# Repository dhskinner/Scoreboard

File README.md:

# Scoreboard
Sports Club Scoreboard

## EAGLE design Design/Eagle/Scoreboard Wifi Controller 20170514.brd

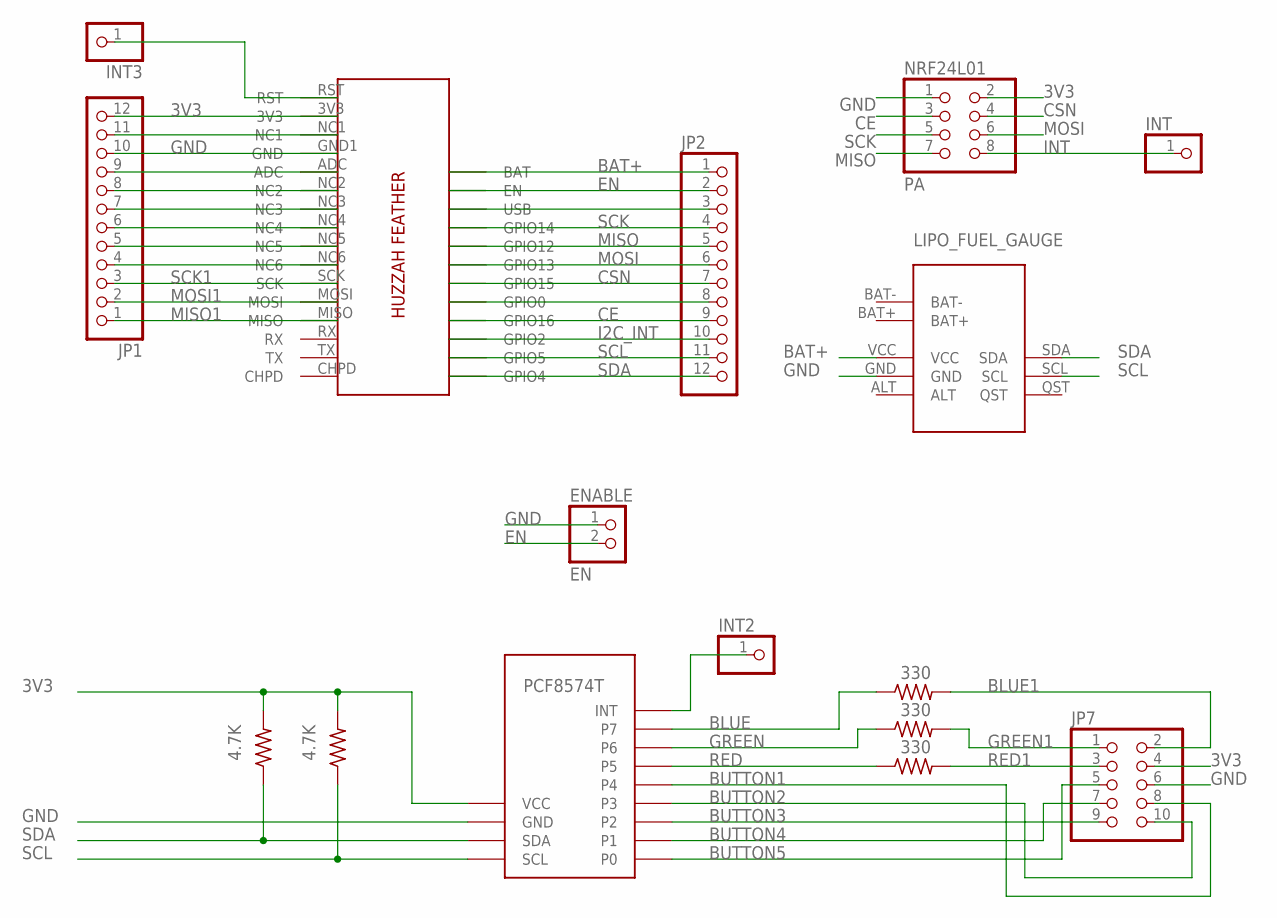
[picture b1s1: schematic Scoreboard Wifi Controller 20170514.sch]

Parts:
ENABLE: EN; 1X02/90
INT, INT2, INT3: PINHD-1X1CB; 1X01-CLEANBIG
JP1, JP2: PINHD-1X12-CB; 1X12-CB
JP7: PINHD-2X5/90; 2X05/90
LIPO_FUEL_GAUGE: LIPO_FUEL_GAUGE
NRF24L01: PA; 2X04/90
R2, R3, R4: 330; 0207/10
R5, R6: 4.7K; 0207/10
U$1: ADAFRUIT-FEATHER-ESP8266-HUZZAHALT; ADAFRUIT-FEATHER-ESP8266-HUZZAH-ALT
U$3: PCF8574T_IO_EXPANDER

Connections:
3V3: JP1.12, JP7.4, NRF24L01.2, R5.2, R6.2, U$1.3V3, U$3.VCC
BAT+: JP2.1, LIPO_FUEL_GAUGE.VCC, U$1.BAT
BLUE: R2.1, U$3.P$7 (P7)
BLUE1: JP7.2, R2.2
BUTTON1: JP7.8, U$3.P$4 (P4)
BUTTON2: JP7.10, U$3.P$3 (P3)
BUTTON3: JP7.9, U$3.P$2 (P2)
BUTTON4: JP7.7, U$3.P$1 (P1)
BUTTON5: JP7.5, U$3.P$0 (P0)
CE: JP2.9, NRF24L01.3, U$1.GPIO16
CSN: JP2.7, NRF24L01.4, U$1.GPIO15
EN: ENABLE.2, JP2.2, U$1.EN
GND: ENABLE.1, JP1.10, JP7.6, LIPO_FUEL_GAUGE.GND, NRF24L01.1, U$1.GND1 (GND), U$3.GND
GREEN: R3.1, U$3.P$6 (P6)
GREEN1: JP7.1, R3.2
I2C_INT: INT2.1, JP2.10, U$1.GPIO2, U$3.INT
INT: INT.1, NRF24L01.8
MISO: JP2.5, NRF24L01.7, U$1.GPIO12
MISO1: JP1.1, U$1.MISO
MOSI: JP2.6, NRF24L01.6, U$1.GPIO13
MOSI1: JP1.2, U$1.MOSI
unnamed: JP1.9, U$1.ADC
unnamed: JP2.8, U$1.GPIO0
unnamed: JP2.3, U$1.USB
unnamed: JP1.8, U$1.NC2
unnamed: JP1.7, U$1.NC3
unnamed: JP1.6, U$1.NC4
unnamed: JP1.5, U$1.NC5
unnamed: JP1.4, U$1.NC6
unnamed: JP1.11, U$1.NC1
RED: R4.1, U$3.P$5 (P5)
RED1: JP7.3, R4.2
RST: INT3.1, U$1.RST
SCK: JP2.4, NRF24L01.5, U$1.GPIO14
SCK1: JP1.3, U$1.SCK
SCL: JP2.11, LIPO_FUEL_GAUGE.SCL, R5.1, U$1.GPIO5, U$3.SCL
SDA: JP2.12, LIPO_FUEL_GAUGE.SDA, R6.1, U$1.GPIO4, U$3.SDA

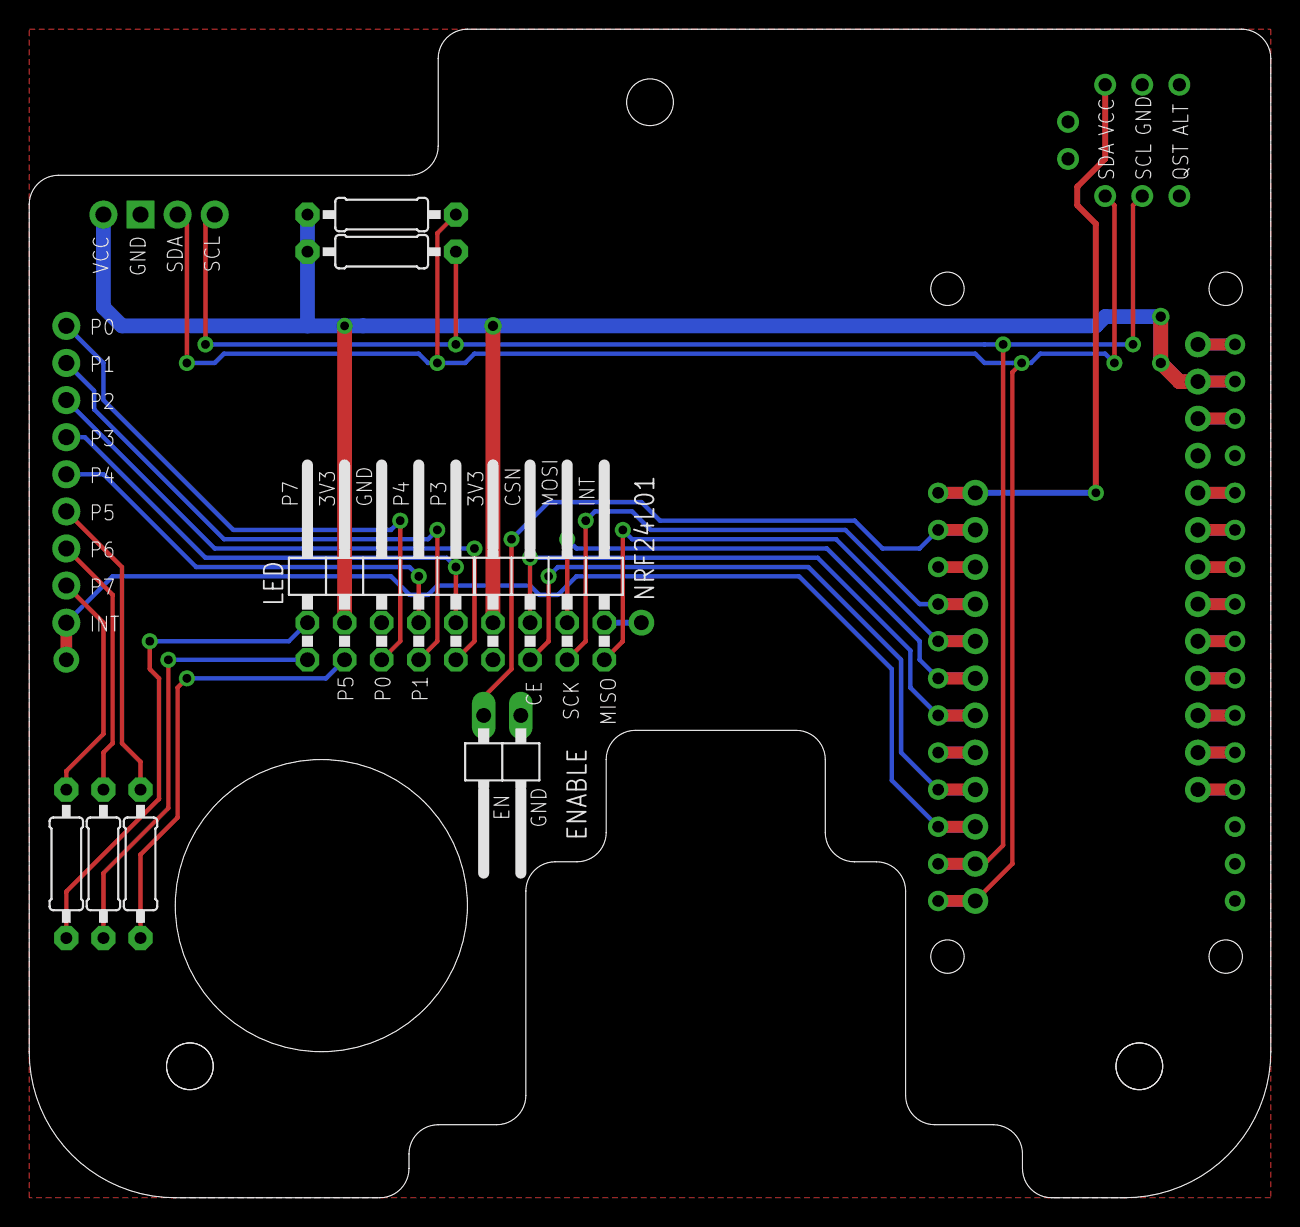
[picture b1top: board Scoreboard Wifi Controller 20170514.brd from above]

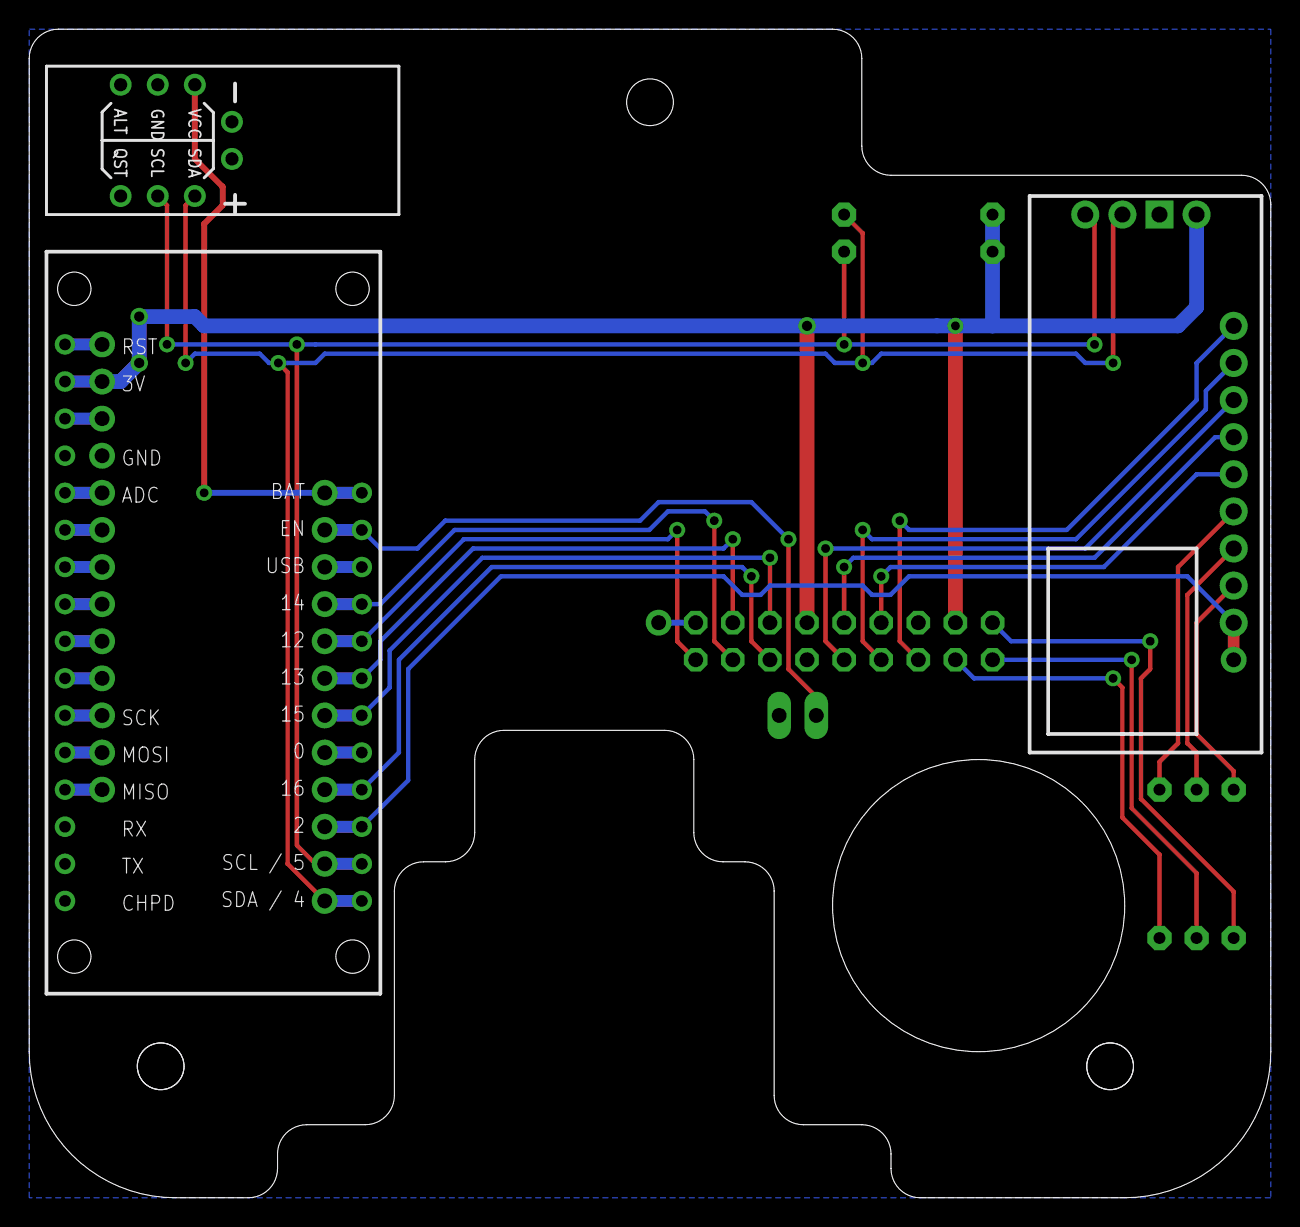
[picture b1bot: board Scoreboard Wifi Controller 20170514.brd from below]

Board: 2 copper layers, 85.0 x 80.0 mm, 16 parts (3 on the bottom side), 37 nets.

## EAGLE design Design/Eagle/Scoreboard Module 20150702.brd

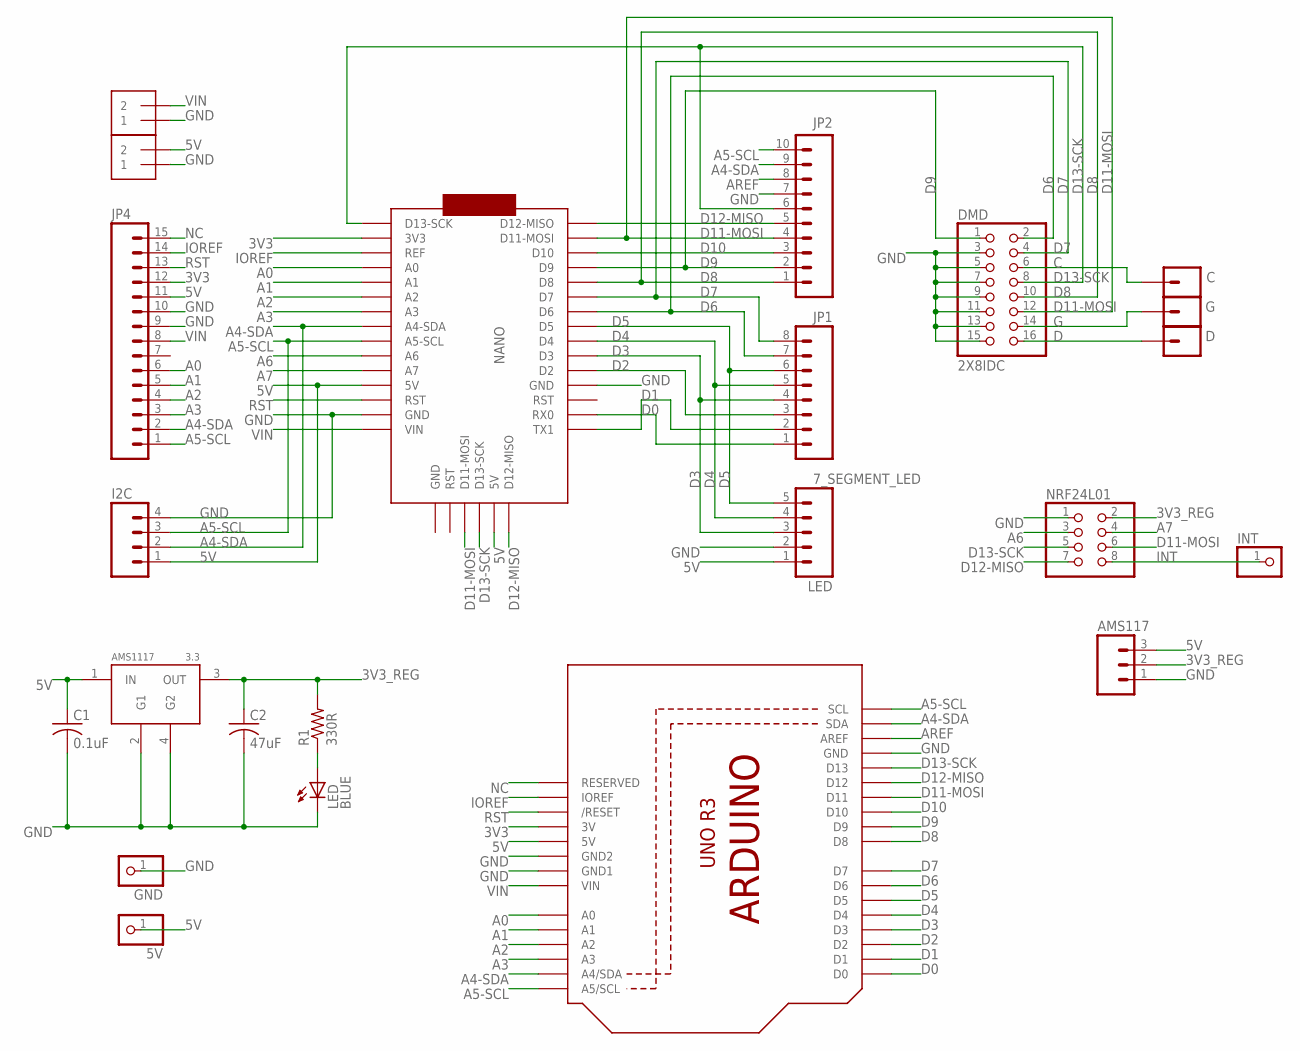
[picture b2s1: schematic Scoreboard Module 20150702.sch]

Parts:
5V: PINHD-1X1; 1X01
7_SEGMENT_LED: LED; 1X05
AMS117: M03PTH; 1X03
AMS1117: 3.3; SOT223
C: M01PTH; 1X01
C1: 0.1uF; C050-035X075
C2: 47uF; C050-035X075
D: M01PTH; 1X01
DMD: 2X8IDC; 2X08-IDC
G: M01PTH; 1X01
GND: PINHD-1X1; 1X01
I2C: M04PTH; 1X04
INT: PINHD-1X1; 1X01
J1, J2: 1X2-3.5MM
JP1: M08SILK_FEMALE_PTH; 1X08
JP2: M10SILK_FEMALE_PTH; 1X10
JP4: M15; 1X15
LED: BLUE; LED3MM
NANO: ARDUINO_NANOICSP; ARDUINO_NANO
NRF24L01: PINHD-2X4; 2X04
R1: 330R; 0204/7
U2: ARDUINOR3-MOVEDTEXT

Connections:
3V3: JP4.12, NANO.P$17 (3V3), U2.3V
3V3_REG: AMS117.2, AMS1117.3 (OUT), C2.1, NRF24L01.2, R1.2
5V: 5V.1, 7_SEGMENT_LED.1, AMS117.3, AMS1117.1 (IN), C1.1, I2C.1, J1.2, JP4.11, NANO.ICSP$2 (5V), NANO.P$27 (5V), U2.5V
A0: JP4.6, NANO.P$19 (A0), U2.A0
A1: JP4.5, NANO.P$20 (A1), U2.A1
A2: JP4.4, NANO.P$21 (A2), U2.A2
A3: JP4.3, NANO.P$22 (A3), U2.A3
A4-SDA: I2C.2, JP2.9, JP4.2, NANO.P$23 (A4-SDA), U2.A4 (A4/SDA), U2.SDA
A5-SCL: I2C.3, JP2.10, JP4.1, NANO.P$24 (A5-SCL), U2.A5 (A5/SCL), U2.SCL
A6: NANO.P$25 (A6), NRF24L01.3
A7: NANO.P$26 (A7), NRF24L01.4
AREF: JP2.8, U2.AREF
C: C.1, DMD.6
D: D.1, DMD.16
D0: JP1.1, NANO.P$2 (RX0), U2.D0
D1: JP1.2, NANO.P$1 (TX1), U2.D1
D2: JP1.3, NANO.P$5 (D2), U2.D2
D3: 7_SEGMENT_LED.3, JP1.4, NANO.P$6 (D3), U2.D3
D4: 7_SEGMENT_LED.4, JP1.5, NANO.P$7 (D4), U2.D4
D5: 7_SEGMENT_LED.5, JP1.6, NANO.P$8 (D5), U2.D5
D6: DMD.2, JP1.7, NANO.P$9 (D6), U2.D6
D7: DMD.4, JP1.8, NANO.P$10 (D7), U2.D7
D8: DMD.10, JP2.1, NANO.P$11 (D8), U2.D8
D9: DMD.1, JP2.2, NANO.P$12 (D9), U2.D9
D10: JP2.3, NANO.P$13 (D10), U2.D10
D11-MOSI: DMD.12, JP2.4, NANO.ICSP$4 (D11-MOSI), NANO.P$14 (D11-MOSI), NRF24L01.6, U2.D11
D12-MISO: JP2.5, NANO.ICSP$1 (D12-MISO), NANO.P$15 (D12-MISO), NRF24L01.7, U2.D12
D13-SCK: DMD.8, JP2.6, NANO.ICSP$3 (D13-SCK), NANO.P$16 (D13-SCK), NRF24L01.5, U2.D13
G: DMD.14, G.1
GND: 7_SEGMENT_LED.2, AMS117.1, AMS1117.2 (G1), AMS1117.4 (G2), C1.2, C2.2, DMD.3, DMD.5, DMD.7, DMD.9, DMD.11, DMD.13, DMD.15, GND.1, I2C.4, J1.1, J2.1, JP2.7, JP4.9, JP4.10, LED.K (C), NANO.P$4 (GND), NANO.P$29 (GND), NRF24L01.1, U2.GND, U2.GND1, U2.GND2
INT: INT.1, NRF24L01.8
IOREF: JP4.14, NANO.P$18 (REF), U2.IOREF
LED: LED.A, R1.1
NC: JP4.15, U2.RESERVED
RST: JP4.13, NANO.P$28 (RST), U2.RESET (/RESET)
VIN: J2.2, JP4.8, NANO.P$30 (VIN), U2.VIN

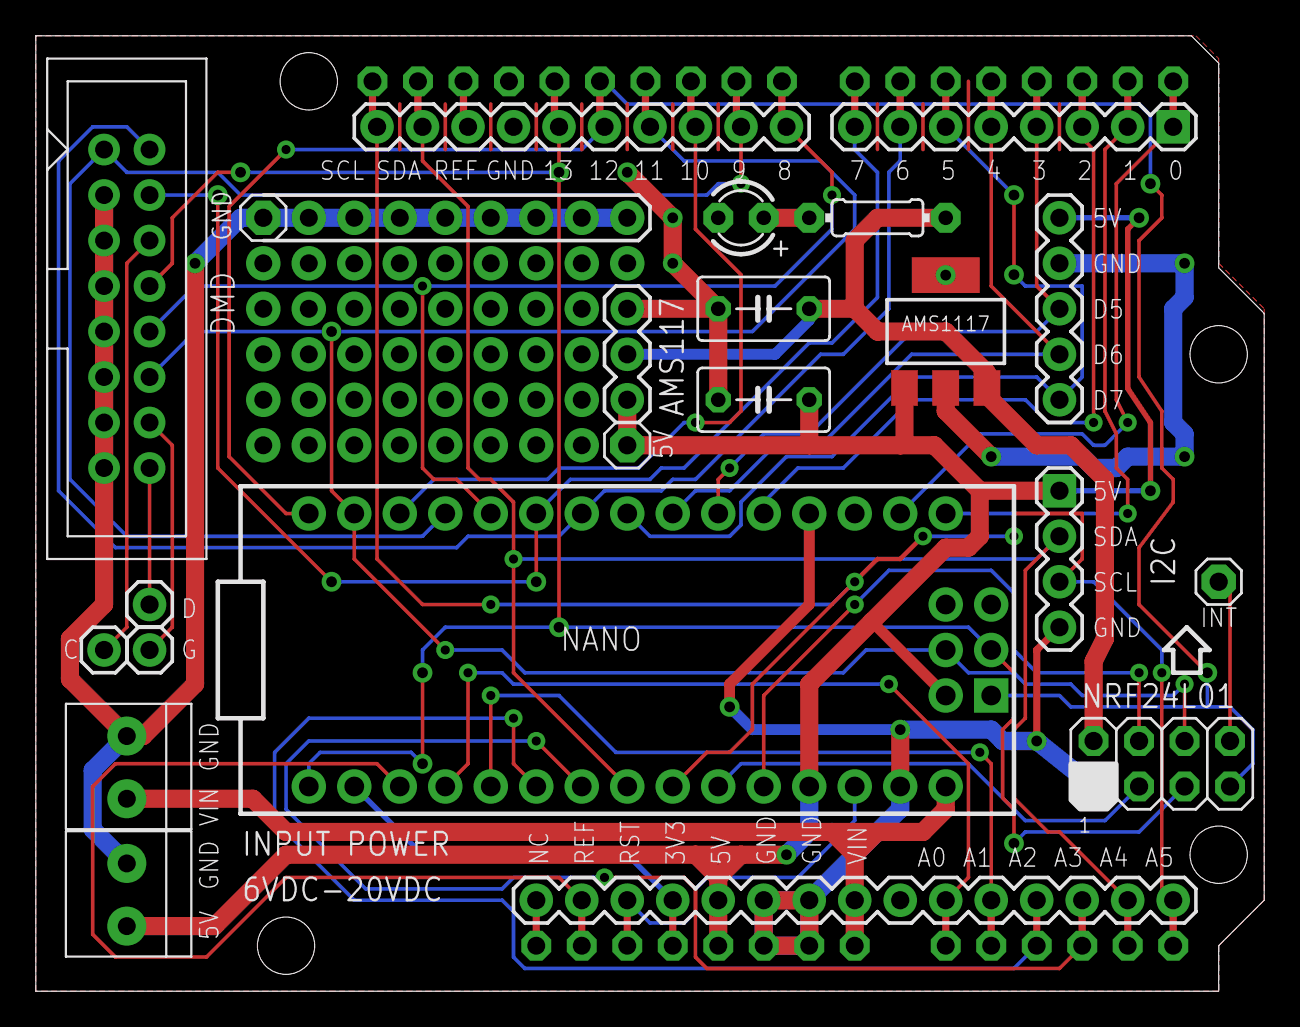
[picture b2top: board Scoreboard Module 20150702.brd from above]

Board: 2 copper layers, 68.6 x 53.3 mm, 23 parts (0 on the bottom side), 36 nets.

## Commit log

2017-08-02 Updated manuals
2017-08-02 Updated 2017 sponsors
2017-08-02 Added design files
2017-08-03 Updated Eagle Files
2017-08-03 Updated firmware (major update)
2018-05-02 Minor updates
2018-05-02 Updated manual April 2018
2018-05-05 Updated instruction card
2018-05-05 Updated manual
2018-05-05 Refreshed 2017 Sponsors
2018-05-05 Synced 2017 Sponsors
2018-05-05 Synced 2018 Sponsors
2019-04-13 Updated with 2019 Sponsors
2020-08-17 Updated 2020 Sponsors
2020-08-17 Updated .gitignore
2020-08-17 Various solidworks updates
2020-08-17 Removed desktop.ini and Thumbs.db
2020-08-22 Updated 2020 Logos
2024-04-10 Sponsors 2023
2024-05-13 Sponsors 2024

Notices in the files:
Design/Eagle/Scoreboard Module 20150702.brd:
COPYRIGHT 2015
parts and their libraries:
SparkFun-Connectors: Licensing: Creative Commons ShareAlike 4.0 International - https://creativecommons.org/licenses/by-sa/4.0
